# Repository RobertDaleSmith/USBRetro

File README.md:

# Joypad OS

<p align="center">
  <picture>
    <source media="(prefers-color-scheme: dark)" srcset="docs/images/logo_solid.svg">
    <source media="(prefers-color-scheme: light)" srcset="docs/images/logo_solid_black.svg">
    
  </picture>
</p>

**Universal controller firmware foundation for adapters, controllers, and input systems.**

Joypad OS is a modular, high-performance firmware platform for building controller adapters, custom controllers, and input/output bridges across USB, Bluetooth, and native game console protocols.

Formerly known as **USBRetro**, this project now serves as the foundational firmware layer of the **Joypad** ecosystem — a universal platform for extending how controllers work, connect, and evolve.

Joypad OS focuses on real-time controller I/O, protocol translation, and flexible routing, making it easy to build everything from classic console adapters to next-generation, assistive, and AI-augmented input devices.

---

## What Joypad OS Enables

- **Universal input/output translation** — Convert USB HID devices into native console protocols and vice versa.
- **Modular firmware apps** — Build specific bridges like `usb2usb`, `usb2gc`, `snes2usb`, passthrough adapters, merged inputs, and hybrid devices — all on a shared core.
- **Flexible routing & passthrough** — Support multi-output controllers, input merging, chaining devices, and advanced mods.
- **Hardware-agnostic foundation** — Designed to run across RP2040 today, with future portability to ESP32 and nRF platforms.
- **Foundation for accessibility & assistive play** — Enables custom controllers and input extensions for gamers with diverse needs.

Joypad OS is the real-time nervous system of the Joypad platform.

---

## Supported Outputs

| Output | Features | Documentation |
|--------|----------|---------------|
| **USB Device** | HID Gamepad, XInput, Xbox OG, Xbox One, PS3, PS4, PS Classic, Switch | [Docs](docs/BUILD.md) |
| **PCEngine / TurboGrafx-16** | Multitap (5 players), Mouse, 2/3/6-button | [Docs](docs/consoles/PCENGINE.md) |
| **GameCube / Wii** | Profiles, Rumble, Keyboard mode | [Docs](docs/consoles/GAMECUBE.md) |
| **Nuon DVD Players** | Controller, Spinner (Tempest 3000), IGR | [Docs](docs/consoles/NUON.md) |
| **3DO Interactive Multiplayer** | 8 players, Mouse, Extension passthrough | [Docs](docs/consoles/3DO.md) |
| **Casio Loopy** | 4 players (experimental) | [Docs](docs/consoles/LOOPY.md) |

---

## Products

Pre-built adapters available at **[controlleradapter.com](https://controlleradapter.com)**:

- **[USB-2-PCE](https://controlleradapter.com/products/usb-2-pce)** - PCEngine/TurboGrafx-16 adapter
- **[GC USB](https://controlleradapter.com/products/gc-usb)** - GameCube/Wii adapter with profiles
- **[NUON USB](https://controlleradapter.com/products/nuon-usb)** - Nuon DVD player adapter

---

## Supported USB Devices

**Controllers:**
- Xbox (OG/360/One/Series X|S)
- PlayStation (Classic/DS3/DS4/DualSense)
- Nintendo Switch (Pro/Joy-Cons)
- 8BitDo (PCE 2.4g, M30, Adapters)
- Generic HID gamepads

**Peripherals:**
- USB Keyboards (full HID support)
- USB Mice (PCEngine mouse, Nuon spinner, 3DO mouse)
- USB Hubs (up to 8 devices for 3DO)

**[Complete hardware compatibility list](docs/HARDWARE.md)**

---

## For Users: Updating Firmware

### Quick Flash

1. **Download** latest `.uf2` from [Releases](https://github.com/joypad-ai/joypad-os/releases)
2. **Enter bootloader**:
   - **USB-2-PCE / NUON / 3DO**: Hold BOOT + connect USB-C
   - **GC USB**: Just connect USB-C (no button)
3. **Drag** `.uf2` file to `RPI-RP2` drive
4. **Done!** Drive auto-ejects when complete

**[Full installation guide](docs/INSTALLATION.md)**

---

## For Developers: Building Firmware

### Quick Start

```bash
# Install ARM toolchain (macOS)
brew install --cask gcc-arm-embedded cmake git

# Clone and initialize
git clone https://github.com/joypad-ai/joypad-os.git
cd joypad-os && make init

# Build specific product
make usb2gc         # GameCube adapter
make usb2pce        # PCEngine adapter
make usb2nuon       # Nuon adapter
make usb23do        # 3DO adapter
```

### Build Commands

```bash
make init          # Initialize submodules (one-time setup)
make all           # Build all products
make clean         # Clean build artifacts

# Build specific products
make usb2pce       # USB2PCE (KB2040 + PCEngine)
make usb2gc        # USB2GC (KB2040 + GameCube)
make usb2nuon      # USB2Nuon (KB2040 + Nuon)
make usb23do       # USB23DO (KB2040 + 3DO)
make usb2loopy     # USB2Loopy (KB2040 + Casio Loopy)
make snes23do      # SNES23DO (SNES→3DO bridge)
```

Output firmware files appear in `releases/` directory.

**[Complete build guide](docs/BUILD.md)**

---

## Documentation

- **[Installation Guide](docs/INSTALLATION.md)** - Flashing firmware, troubleshooting
- **[Hardware Compatibility](docs/HARDWARE.md)** - Supported controllers, boards, DIY builds
- **[Build Guide](docs/BUILD.md)** - Developer setup, architecture

### Console-Specific Guides

- **[GameCube/Wii](docs/consoles/GAMECUBE.md)** - Profiles, keyboard mode, rumble
- **[PCEngine/TurboGrafx-16](docs/consoles/PCENGINE.md)** - Multitap, mouse, button modes
- **[Nuon](docs/consoles/NUON.md)** - Controller, Tempest 3000 spinner, IGR
- **[3DO](docs/consoles/3DO.md)** - 8-player support, mouse, profiles
- **[Casio Loopy](docs/consoles/LOOPY.md)** - Experimental support

---

## Architecture

Joypad OS uses a modular architecture:

- **RP2040** - Dual-core ARM Cortex-M0+ microcontroller
- **TinyUSB** - USB host stack for polling USB devices
- **PIO** - Programmable I/O for timing-critical console protocols
- **Dual-Core**: Core 0 handles USB input, Core 1 runs console output
- **Router** - Flexible input→output routing (SIMPLE/MERGE/BROADCAST)
- **Apps** - Per-product configuration (router, profiles, features)

**See [CLAUDE.md](CLAUDE.md) for detailed architecture**

---

## Community & Support

- **Discord**: [community.joypad.ai](http://community.joypad.ai/) - Community chat
- **Issues**: [GitHub Issues](https://github.com/joypad-ai/joypad-os/issues) - Bug reports
- **Email**: support@controlleradapter.com - Product support

---

## Acknowledgements

- [Ha Thach](https://github.com/hathach/) - [TinyUSB](https://github.com/hathach/tinyusb)
- [David Shadoff](https://github.com/dshadoff) - [PCEMouse](https://github.com/dshadoff/PC_Engine_RP2040_Projects/tree/main/PCEMouse) foundation
- [FCare](https://github.com/FCare) - [USBTo3DO](https://github.com/FCare/USBTo3DO) 3DO protocol implementation
- [Ryzee119](https://github.com/Ryzee119) - [tusb_xinput](https://github.com/Ryzee119/tusb_xinput/)
- [SelvinPL](https://github.com/SelvinPL/) - [lufa-hid-parser](https://gist.github.com/SelvinPL/99fd9af4566e759b6553e912b6a163f9)
- [JonnyHaystack](https://github.com/JonnyHaystack/) - [joybus-pio](https://github.com/JonnyHaystack/joybus-pio)

---

## License

Joypad OS is licensed under the **Apache-2.0 License**.

The **Joypad** name and branding are trademarks of Joypad Inc.

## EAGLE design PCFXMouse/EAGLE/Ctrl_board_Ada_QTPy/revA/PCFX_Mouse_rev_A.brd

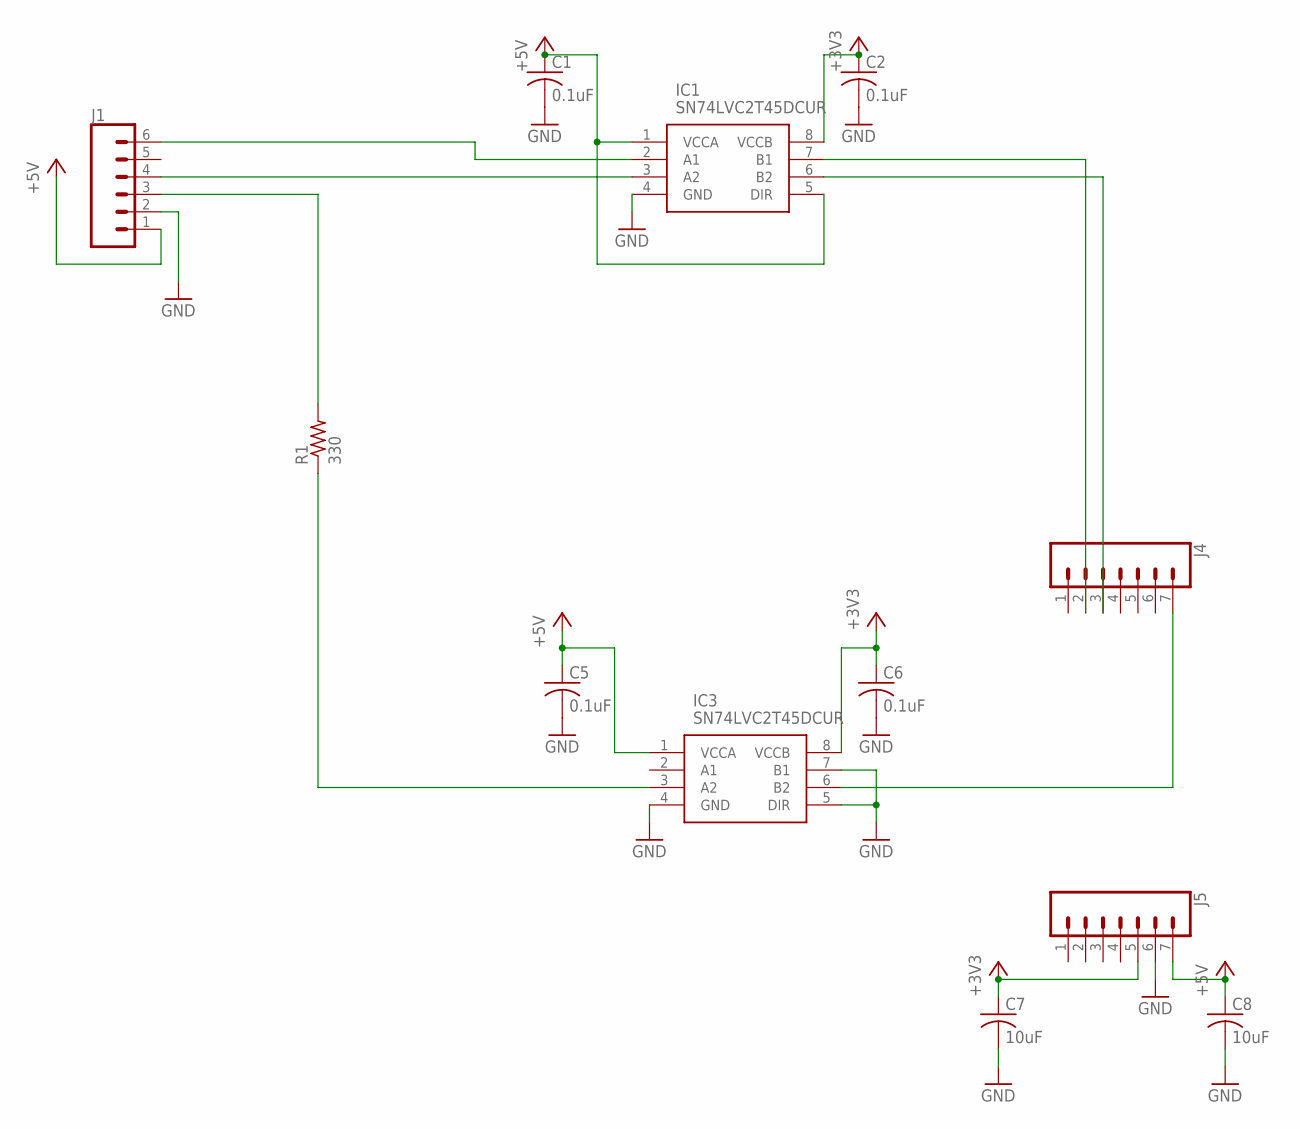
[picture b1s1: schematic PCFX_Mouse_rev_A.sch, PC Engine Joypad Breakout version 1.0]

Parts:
C1, C2, C5, C6: 0.1uF; C0402
C7, C8: 10uF; C0805
IC1, IC3: SN74LVC2T45DCUR; SOP50P310X90-8N
J1: CONN_06NO_SILK_FEMALE_PTH; 1X06_NO_SILK
J4, J5: CONN_07LONGPADS; 1X07_LONGPADS
R1: 330; R0402

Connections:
+3V3: C2.1, C6.1, C7.1, IC1.8 (VCCB), IC3.8 (VCCB), J5.5
+5V: C1.1, C5.1, C8.1, IC1.1 (VCCA), IC1.5 (DIR), IC3.1 (VCCA), J1.1, J5.7
CLK: IC1.3 (A2), J1.4
DATA: J1.3, R1.2
GND: C1.2, C2.2, C5.2, C6.2, C7.2, C8.2, IC1.4 (GND), IC3.4 (GND), IC3.5 (DIR), IC3.7 (B1), J1.2, J5.6
LATCH: IC1.2 (A1), J1.6
unnamed: IC1.7 (B1), J4.2
unnamed: IC3.6 (B2), J4.7
unnamed: IC1.6 (B2), J4.3
unnamed: IC3.3 (A2), R1.1

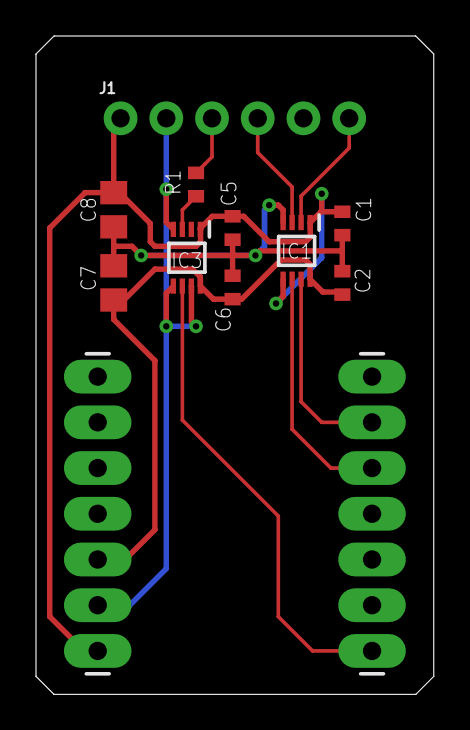
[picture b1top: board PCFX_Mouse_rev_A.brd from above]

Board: 2 copper layers, 22.1 x 36.6 mm, 12 parts (0 on the bottom side), 10 nets.

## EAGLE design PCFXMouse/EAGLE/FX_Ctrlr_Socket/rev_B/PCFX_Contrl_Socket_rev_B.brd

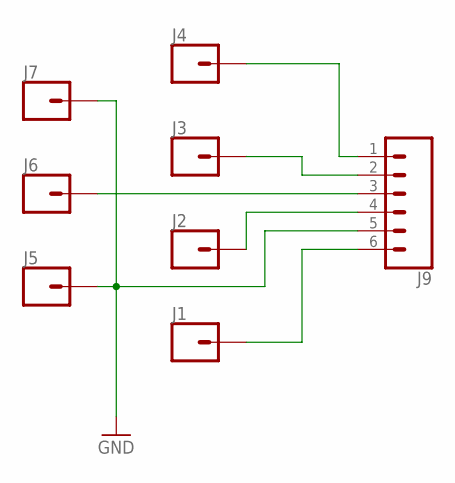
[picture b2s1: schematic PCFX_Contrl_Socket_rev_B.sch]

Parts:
J1, J2, J3, J4, J5, J6, J7: CONN_01PTH_NO_SILK_YES_STOP; 1X01_NO_SILK
J9: CONN_06NO_SILK_FEMALE_PTH; 1X06_NO_SILK

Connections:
GND: J5.1, J7.1, J9.5
unnamed: J4.1, J9.1
unnamed: J3.1, J9.2
unnamed: J6.1, J9.3
unnamed: J2.1, J9.4
unnamed: J1.1, J9.6

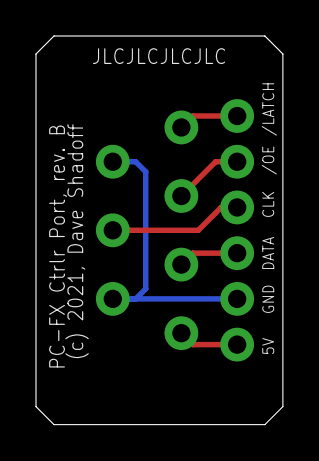
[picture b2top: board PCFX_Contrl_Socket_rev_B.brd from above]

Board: 2 copper layers, 13.7 x 21.6 mm, 8 parts (0 on the bottom side), 6 nets.

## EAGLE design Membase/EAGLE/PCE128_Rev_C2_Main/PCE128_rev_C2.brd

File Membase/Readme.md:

# PC_Engine_RP2040_Projects - Memory Base 128 reimplementation

## Overview

This is the third implementation of the Memory Base 128 I have written for modern hardware, and the easiest code to read/follow.
The PIOs on the Raspberry Pi Pico microcontroller are used for edge-sensing of the data input, and the ARM core is used for processing.

The data is loaded into SRAM at startup, and saved into Flash after transactions take place.  This may not be ideal, as the
device is not capable of processing additional commands while the Flash flush is in progress (it takes place 0.75 seconds
after the last read/write of a group of read or write transactions).  While this flush is taking place, the PIO state machine
is shut down, so there won't be a backlog of bits causing confusion; however, if any transactions take place during the period of
flash write, they won't be recognized, and the PC Engine game may identify an error.

Status is displayed by LEDs on the main board, recessed into the device, adjacent to the joypad connector:

Yellow (Left) = Device active  
Green (Right) = Read  
Red (Right) = Write  
Blue (Left) = Delayed commit to Flash memory  

## Source Code

This was built using Pico-SDK version 1.2.0
pico_sdk_import.cmake is from the SDK, but is required by CMake (and thus replicated here)

To build the source, first ensure that you have the right version of the RaspberryPi/piso-sdk installed.
As this board targets the Adafruit QtPy2040 board, you should run the make_ada.sh script (under UNIX), or from
the command-line:  
"cmake -DPICO_BOARD=adafruit_qtpy_rp2040 -B build"  
Then, "cd build" and "make".

I have also included a release version of the program as a uf2 file in the releases/ folder; just drag and drop it
onto the virtual drive presented when putting the board into BOOTSEL mode (holding the 'boot' button, connect the
board by USB to a host computer, and release the button; a new drive should appear on the computer).

## PC Board & Assembly

I designed all boards using the free version of EAGLE (2-layer, less than 100mm on both X- and Y- axes).
The gerbers are included in this repository, in case you want to get your own set made.

I have included the gerbers and relevant bom.csv and assembly.csv files to get these boards
assembled by JLCPCB, but you will still need the following parts:
- (2) 8-pin Mini-DIN connectors
- (1) Adafruit QtPy RP2040 microcontroller board
- (2) 7-pin headers.  You may also want to use female pin header sockets in case you need to remove the microcontroller board.
I recommend using short/low-profile header sockets in this case.

You will also need some mounting hardware for the board stack-up:
- (4) M3 x 13mm female-female standoffs; flat side-to-flat side should be no larger tha 5.0mm, as the mounting holes are made for this size.  (4.5mm are fine too)
- (8) M3 screws, 6mm in length (*) - these may need to be longer if you don't trim the through-hole leads flush to the board.
- optional rubber/silicone feet

And for use, you will also need a short 8-pin mini-DIN male-male cable (various lengths can be found on ebay).

### Assembly

The "case" is made up of stacked PC boards, with PC boards on the top and bottom; There are 5 different boards in all, but 13 layers as follows:
1. Top = 1 layer, 1.6mm thick, ENIG board, in "PCE128_Rev_C_Face"  
2. MidTop = 6 layers, 1.6mm thick, HASL board in "PCE128_Rev_C_MidTop"  
3. MidLow = 3 layers, 1.2mm thick, HASL board in "PCE128_Rev_C_MidLow" (looks similar to MidTop, but has cutouts for the LEDs)  
4. Main Board = 1 layer, 1.6mm thick, HASL, SMD assembly board in "PCE128_Rev_C2_Main" (Note: some parts have been shifted from the previous "B" version; they are not interchangeable)  
5. Sub = 1 layer, 0.8mm thick (*), HASL board in "PCE128_Rev_C_Sub"  
6. Bottom = 1 layer, 1.6mm thick, ENIG board in "PCE128_Rev_C_Face" (reverse side faces out)  

(*) Note that I trim the through-hole leads flush to the board, which enables a thin "Sub" layer, which exists only to make space for the through-hole portions; if you do not trim these flush, you may need a much thicker Sub layer, and longer M3 screws.

Steps to assembly:
1. Trim the leads of the through-hole parts carefully, to minimize the solder "bump" on the underside of the board when mounted.  The through-hole parts to be mounted include the 8-pin mini-DIN sockets, and the headers (or sockets) for the RP2040 board.  **Make sure that the mini-DIN connectors are mounted straight, or the upper-layer boards may have trouble being placed.**
2. Solder carefully, miniizing the amount of "bump" below the board
3. With the LEDs closest to you, mount the RP2040 board with the USB connector on the right side
4. Connect it to a host computer while holding the "Boot" button down.  This will put it in DFU mode and create a virtual drive on the host computer.  Drag and drop the *.uf2 firmware file into that folder.  A moment later, the virtual drive should disappear and after about 1 second, all four LEDs should light up briefly as part of the boot sequence of the memory device.  Disconnect it from USB.

For the board stack-up, it is best to connect the lower boards first, with the screws going through the bottom layers of board, into one side of the female-female standoffs.  Then, the upper layer boards can simply be stacked, and the top screws tightened easily.

And one final touch: the edges of the PC boards are a different shade than the front/back surfaces, creating a two-tone effect which you may or may not like.  In order to make the case look more like a uniform "black box", I have used a Sharpie marker along the edge of the PC Boards to darken them.  The shade is similar to JLCPCB's matte black solder mask, so it should be a good match in areas with standard lighting.  The Sharpie ink, being permanent, won't run when it gets wet, but be careful near any alcohol-based solvents; the ink may run/stain in such situations.

Here is a visual view:

## Notes
I have tried to use the Adafruit QtPy RP2040 as much as possible, as it is a compact form factor which is easy to design around.

Unfortunately, the Adafruit site tries to direct all users toward CircuitPython rather than the Pi SDK, and
as a result, Pinout pages of the "Pinout" page for their RP2040 devices don't include references to the GPIO numbers.

Therefore, I am including a graphic here:

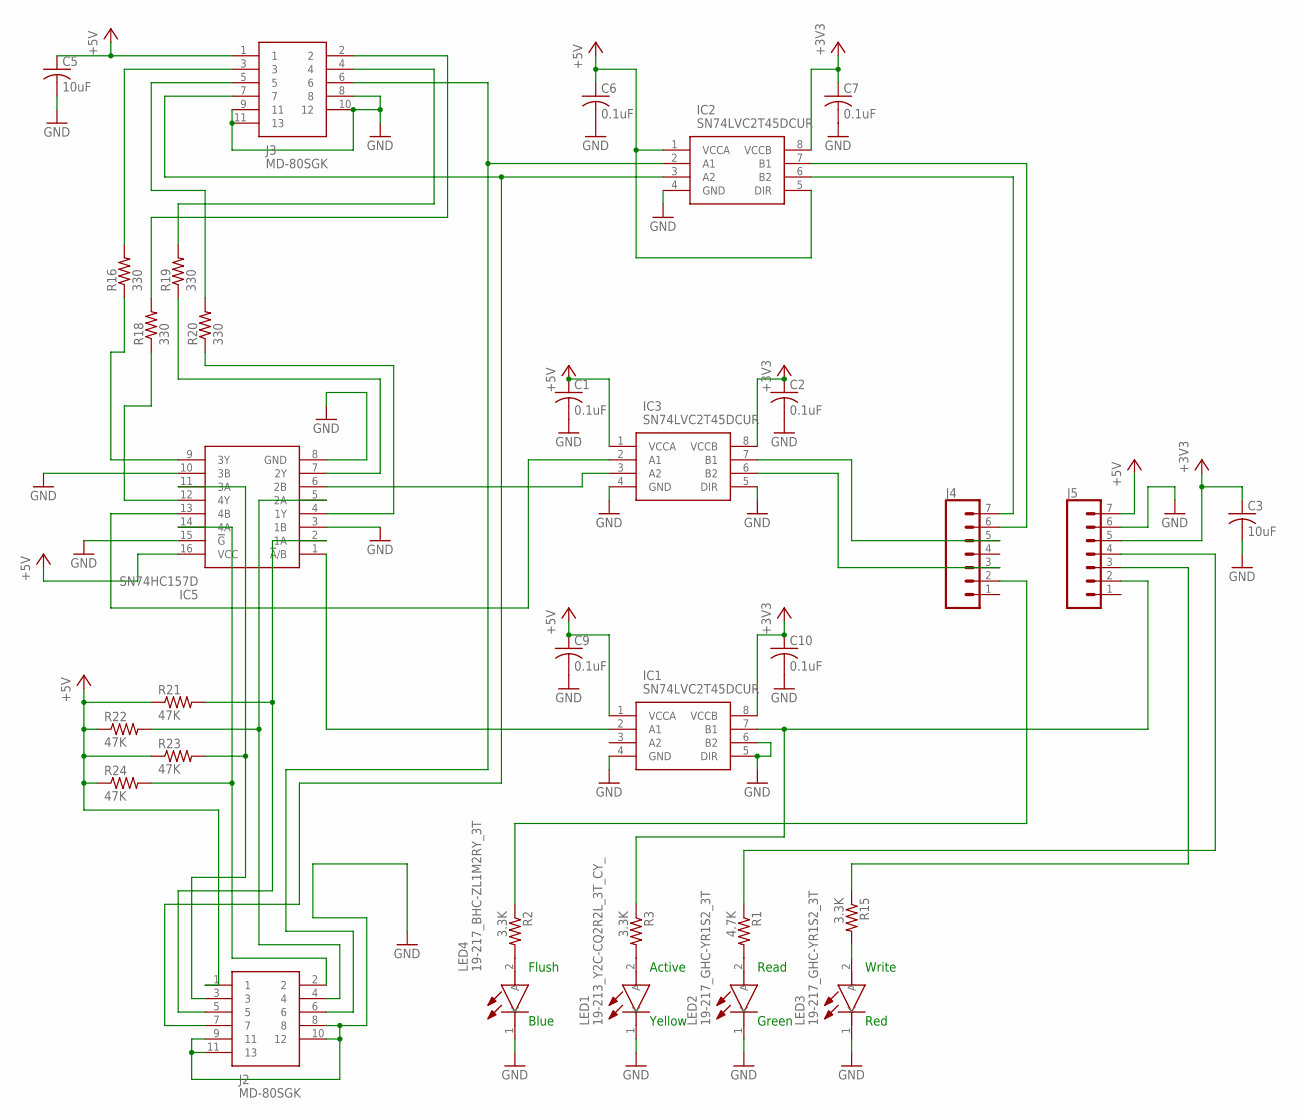
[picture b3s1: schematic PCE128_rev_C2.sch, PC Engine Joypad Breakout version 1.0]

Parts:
C1, C2, C6, C7, C9, C10: 0.1uF; C0402
C3, C5: 10uF; C0805
IC1, IC2, IC3: SN74LVC2T45DCUR; SOP50P310X90-8N
IC5: SN74HC157D; SOIC127P600X175-16N
J2, J3: MD-80SGK; MD80SGK
J4, J5: CONN_07NO_SILK; 1X07_NO_SILK
LED1: 19-213_Y2C-CQ2R2L_3T_CY_; LEDC1608X50N
LED2: 19-217_GHC-YR1S2_3T; LEDC1608X50N
LED3: 19-217_GHC-YR1S2_3T; LEDC1608X50N; MANUFACTURER_PART_NUMBER KT-0603R
LED4: 19-217_BHC-ZL1M2RY_3T; LEDC1608X50N
R1: 4.7K; R0402
R2, R3, R15: 3.3K; R0402
R16, R18, R19, R20: 330; R0402
R21, R22, R23, R24: 47K; R0402

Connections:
+3V3: C2.1, C3.1, C7.1, C10.1, IC1.8 (VCCB), IC2.8 (VCCB), IC3.8 (VCCB), J5.5
+5V: C1.1, C5.1, C6.1, C9.1, IC1.1 (VCCA), IC2.1 (VCCA), IC2.5 (DIR), IC3.1 (VCCA), IC5.16 (VCC), J2.1, J3.1, J5.7, R21.1, R22.1, R23.1, R24.1
CLR: IC2.3 (A2), J2.7, J3.7
D0_IN: IC5.14 (4A), J2.2, R24.2
D0_OUT: J3.2, R18.2
D1_IN: IC5.11 (3A), J2.3, R23.2
D1_OUT: J3.3, R16.2
D2_IN: IC5.5 (2A), J2.4, R22.2
D2_OUT: J3.4, R19.2
D3_IN: IC5.2 (1A), J2.5, R21.2
D3_OUT: J3.5, R20.2
D6: J5.3, R15.1
D10: J5.4, R1.1
D11: IC1.7 (B1), J5.2, R3.1
GND: C1.2, C2.2, C3.2, C5.2, C6.2, C7.2, C9.2, C10.2, IC1.4 (GND), IC1.5 (DIR), IC1.6 (B2), IC2.4 (GND), IC3.4 (GND), IC3.5 (DIR), IC5.3 (1B), IC5.8 (GND), IC5.10 (3B), IC5.15 (!G), J2.8, J2.9 (11), J2.10 (12), J2.11 (13), J3.8, J3.9 (11), J3.10 (12), J3.11 (13), J5.6, LED1.1 (K), LED2.1 (K), LED3.1 (K), LED4.1 (K)
unnamed: LED2.2 (A), R1.2
unnamed: J4.2, R2.1
unnamed: IC3.7 (B1), J4.5
unnamed: LED4.2 (A), R2.2
unnamed: LED1.2 (A), R3.2
unnamed: IC3.6 (B2), J4.3
unnamed: IC3.3 (A2), IC5.6 (2B)
unnamed: IC2.7 (B1), J4.6
unnamed: IC1.2 (A1), IC5.1 (!A!/B)
unnamed: IC5.9 (3Y), R16.1
unnamed: IC5.12 (4Y), R18.1
unnamed: IC5.4 (1Y), R20.1
unnamed: IC5.7 (2Y), R19.1
unnamed: IC3.2 (A1), IC5.13 (4B)
unnamed: IC2.6 (B2), J4.7
unnamed: LED3.2 (A), R15.2
SEL: IC2.2 (A1), J2.6, J3.6

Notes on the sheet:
Active
Read
Write
Yellow
Green
Red
Blue
Flush

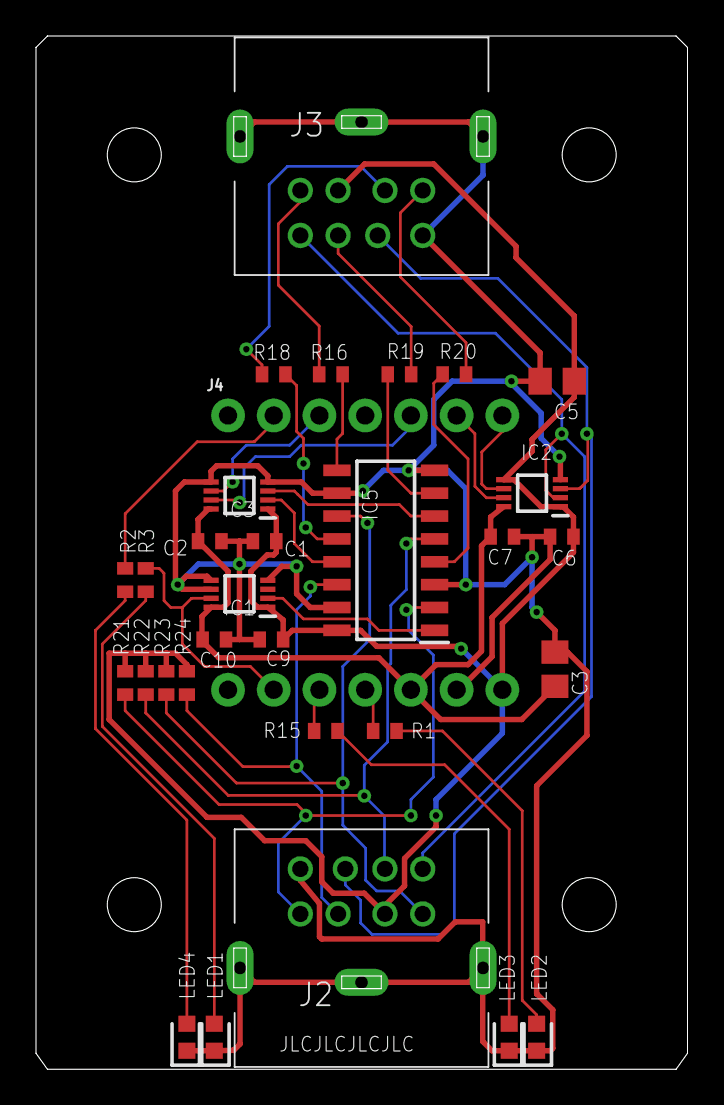
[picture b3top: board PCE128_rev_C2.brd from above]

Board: 2 copper layers, 36.2 x 57.4 mm, 32 parts (0 on the bottom side), 32 nets.

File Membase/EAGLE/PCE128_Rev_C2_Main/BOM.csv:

Qty,Designator,Footprint,Comment,LCSC Part # (optional),Description (optional)
2,"J2, J3",MD80SGK,Do not mount,Do not mount,"Circular DIN Connectors mini-DIN, 8P jack, rt, through hole, full shield"
2,"J4, J5",1X07_NO_SILK,Do not mount,Do not mount,Multi connection point. Often used as Generic Header-pin footprint for 0.1 inch spaced/style header connections
6,"C1, C2, C6, C7, C9, C10",C0402,100nF 16V,C1525,Samsung CL05B104KO5NNNC 100nF 16V 0402
2,"C3, C5",C0805,10uF 25V,C15850,Samsung CL21A106KAYNNNE  10uF 25V 0805
1,LED1,LEDC1608X50N,Yellow,C72038,Everlight Elec 19-213/Y2C-CQ2R2L/3T(CY)  0603
1,LED2,LEDC1608X50N,Green,C72043,Everlight Elec 19-217/GHC-YR1S2/3T  0603
1,LED3,LEDC1608X50N,Red,C2286,Hubei KENTO Elec  KT-0603R  0603
1,LED4,LEDC1608X50N,Blue,C72041,Everlight 19-217/BHC-ZL1M2RY/3T  0603
1,R1,R0402,4.7K,C25900,Uniroyal Elec  0402WGF4701TCE  0402
3,"R2, R3, R15",R0402,3.3K,C25890,Uniroyal Elec  0402WGF3301TCE  0402
4,"R16, R18, R19, R20",R0402,330R,C25104,Uniroyal Elec  0402WGF3300TCE  0402
4,"R21, R22, R23, R24",R0402,47K,C25792,Uniroyal Elec  0402WGF4702TCE  0402
3,"IC1, IC2, IC3",VSSOP-8_2.0x2.3x0.5P,SN74LVC2T45DCUR,C15741,"Texas Instruments SN74LVC2T45DCUR, Voltage Level Translator, Bus Transceiver, 3-State, 1.65  5.5 V, 8-Pin UM"
1,IC5,SOIC-16_3.9x9.9x1.27P,SN74HC157D,C6823,Quadruple 2-Line To 1-Line Data Selectors/Multiplexers

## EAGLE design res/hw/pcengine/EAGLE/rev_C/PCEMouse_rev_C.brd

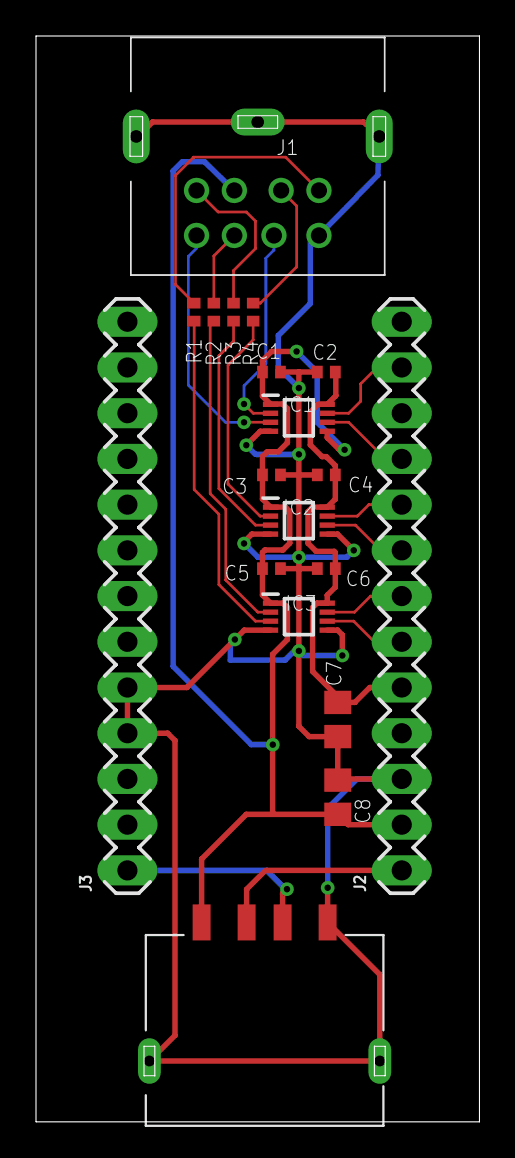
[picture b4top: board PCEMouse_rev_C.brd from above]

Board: 2 copper layers, 24.6 x 60.3 mm, 19 parts (0 on the bottom side), 21 nets.

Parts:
C1, C2, C3, C4, C5, C6: 0.1uF; C0402
C7, C8: 10uF; C0805
IC1, IC2, IC3: SN74LVC2T45DCUR; SOP50P310X90-8N
J1: MD-80SGK; MD80SGK
J2, J3: 1X13-LONGPADS
R1, R2, R3, R4: 330; R0402
U$1: 912-121A2026S10100

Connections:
+3V3: C2.1, C4.1, C6.1, C7.1, IC1.8, IC2.8, IC3.8, J2.5
+5V: C1.1, C3.1, C5.1, C8.1, IC1.1, IC1.5, IC2.1, IC3.1, J1.1, J2.2, U$1.VCC
CLR: IC1.2, J1.7
D0_OUT: J1.2, R4.2
D1_OUT: J1.3, R3.2
D2_OUT: J1.4, R2.2
D3_OUT: J1.5, R1.2
GND: C1.2, C2.2, C3.2, C4.2, C5.2, C6.2, C7.2, C8.2, IC1.4, IC2.4, IC2.5, IC3.4, IC3.5, J1.8, J1.9, J1.10, J1.11, J2.3, J3.4, J3.5, U$1.GND, U$1.P$5, U$1.P$6
GPIO18: IC1.6, J2.10
GPIO19: IC1.7, J2.12
GPIO26: IC2.7, J2.9
GPIO27: IC2.6, J2.8
GPIO28: IC3.7, J2.7
GPIO29: IC3.6, J2.6
unnamed: J3.1, U$1.D+
unnamed: IC3.3, R1.1
unnamed: IC3.2, R2.1
unnamed: IC2.3, R3.1
unnamed: IC2.2, R4.1
unnamed: J2.1, U$1.D-
SEL: IC1.3, J1.6

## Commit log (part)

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2025-12-05 Add missing app_task to snes23do
2025-12-05 Add usb2usb_rp2040zero target for RP2040-Zero boards
    Adds support for USB host on RP2040-Zero with PIO USB pins:
    - D+ on GPIO 10, D- on GPIO 11 (compatible with ogx-mini hardware)
    - NeoPixel on GPIO 16
    PIO USB pin configuration is now defined at the board/target level
    via CONFIG_PIO_USB_DP_PIN, making it easy to add other board variants.
    Build with: make usb2usb_rp2040zero
2025-12-05 Add button GPIO definition for usb2usb_rp2040zero (GPIO 14)
2025-12-05 Refactor CMakeLists.txt to reduce duplication
    - Add source lists (CORE_SOURCES, USB_HOST_SOURCES, USB_DEVICE_SOURCES, etc.)
    - Add library lists (COMMON_LIBRARIES, CONTROLLER_LIBRARIES)
    - Add helper function usbretro_target_common() for common target setup
    - Organize targets into sections by app type
    - Reduce file from ~675 lines to ~432 lines
2025-12-10 Fix L1/R1/L2/R2 button mapping in PSC output interface
2025-12-11 Add DS3 Bluetooth support
    - DS3 BT driver with enable_sixaxis activation and input parsing
    - Skip authentication for DS3 (uses COD-based detection)
    - ACL deferred send pattern for USB endpoint busy handling
    - USB DS3 programming flow: wait for button press, program dongle address
    - Cache local BD_ADDR to flash for DS3 programming when dongle unplugged
    - Add bt_task() call to main loop for BT HID driver tasks
2025-12-11 Add rumble support for DS3 Bluetooth
2025-12-12 Add separate left/right rumble and LED feedback to output interface
2025-12-12 Add motion data passthrough for DS3/DS4/DS5 controllers
    - Add accel[3], gyro[3], has_motion fields to input_event_t and profile_output_t
    - Parse motion data in DS3 USB/BT drivers (bytes 40-47, big-endian 16-bit)
    - Parse motion data in DS4/DS5 USB/BT drivers from existing struct fields
    - Output motion in PS3 output interface with big-endian byte order
    - Fix router MERGE_BLEND mode to copy motion from first device with motion data
    - Adjust PS3 input report to 50 bytes for correct motion byte alignment
2025-12-12 Add DS3 pressure-sensitive button passthrough
    Parse all 12 pressure values from DS3 USB and BT input reports:
    - D-pad: up, right, down, left
    - Triggers/bumpers: L2, R2, L1, R1
    - Face buttons: triangle, circle, cross, square
    Added pressure[12] and has_pressure to input_event_t and
    profile_output_t. PS3 output mode now uses actual pressure
2025-12-12 Add stick modifier system for button-triggered sensitivity changes
    - Add stick_modifier_t struct for button-triggered sensitivity modifiers
    - Add left/right_stick_modifiers arrays to profile_t
    - Update profile_apply() to check modifiers before applying sensitivity
    - First matching modifier wins, can optionally consume trigger button
    - Add STICK_MODIFIER() and STICK_MODIFIER_KEEP() helper macros
    - SSBM profile: L3 reduces left stick to 50% for walk mode
2025-12-12 Rename USBRetro to Joypad
    - USBR_BUTTON_* → JP_BUTTON_* across all files
    - USBRetro references → Joypad in comments/strings
    - Completes rebranding to match new project name
2025-12-12 Add ASCII controller diagram to buttons.h
    Shows button positions with W3C index numbers for quick reference.
2025-12-12 Add A4 placeholder button
2025-12-12 Update README for Joypad Core rebrand
2025-12-12 Update repo URLs to joypad-ai/joypad-core
2025-12-12 Remove Xbox One S from supported consoles
2025-12-12 Remove DragonRise from supported devices
2025-12-12 Update CLAUDE.md: add flash commands, profile system, USBRetro context; remove USB-2-3DO product
2025-12-12 Rename Supported Consoles to Supported Outputs, add USB HID
2025-12-12 Add Xbox One to USB outputs
2025-12-12 DS4 BT: add rumble, motion, LED support; rename USBR to Joypad
    - Add feedback system integration for rumble passthrough
    - Add motion data passthrough (gyro/accel) when sixaxis enabled
    - Add player LED colors: P1=blue, P2=red, P3=green, P4=pink
    - Support both RGB LED and player LED pattern from host
    - Activation state machine with proper delays
    - Rename USB device strings: USBR → Joypad (DInput, XAC, Data, Debug)
2025-12-12 BLE: Add extended scanning and connection for Xbox Series controllers
    - Add BLE extended scanning (HCI 0x2041/0x2042) for BT 5.0+ dongles
    - Add LE Extended Create Connection (0x2043) command
    - Fix HCI event mask to include LE Meta Event (bit 61)
    - Parse BLE advertising data to extract device names
    - Auto-detect and connect to Xbox Wireless Controller
    - Proper sequencing: cancel inquiry -> stop scan -> connect
2025-12-13 BLE: Add SMP pairing for encrypted HID access
    Xbox BLE controllers require encryption before allowing HID access.
    When ATT receives error 0x0F (Insufficient Encryption), SMP pairing
    is automatically initiated.
    SMP Implementation:
    - "Just Works" pairing (no user interaction required)
    - AES-128 encryption for c1 confirm and s1 STK generation
2025-12-15 BTstack: Use standard listener API, remove gatt_client.c hook
    Switch from custom gatt_client.c hook to standard BTstack API:
    - gatt_client_listen_for_characteristic_value_updates() works correctly
    - Register listener after SM_EVENT_PAIRING_COMPLETE and REENCRYPTION_COMPLETE
    - Deferred processing pattern preserved (copy to buffer, process in main loop)
    Root cause of previous freeze was printf inside __not_in_flash_func,
    not the BTstack listener API itself.
2025-12-15 BTstack: Add Classic BT HID Host support
    Wire BTstack's hid_host.c to existing bthid driver layer:
    - Initialize hid_host_init() with HID descriptor storage
    - Add classic inquiry scanning alongside BLE scanning
    - Handle GAP_EVENT_INQUIRY_RESULT to detect gamepads (COD 0x05xx)
    - Auto-connect to gamepads/joysticks with hid_host_connect()
    - Handle HID_SUBEVENT_* events for connection lifecycle:
2025-12-15 Implement user button hold to clear all BT bonds
    - Add btstack_host_delete_all_bonds() to clear Classic and BLE bonds
    - Hold user button (1.5s) triggers bond clearing
    - Clears Classic BT link keys via gap_delete_all_link_keys()
    - Clears BLE bonds via le_device_db_init()
2025-12-15 Fix DS4/DS5 Bluetooth reconnection
    - Add SDP server with Device ID record (required for Sony reconnect)
    - Handle link key storage and reply manually for incoming connections
    - Request remote name on incoming for proper driver matching
    - Let device initiate HID channels on reconnect (not host)
2025-12-16 Query SDP VID/PID for outgoing Classic BT connections
    Previously SDP Device ID query was only triggered for incoming
    connections. Now also query VID/PID when HID connection opens
    for outgoing (inquiry-based) connections.
    - Start SDP query at HID_SUBEVENT_CONNECTION_OPENED if VID/PID unknown
    - Request remote name if not available from inquiry EIR data
    - Update connection struct when SDP query and name request complete
2025-12-16 feat: BTstack modularization, PCEngine fixes, wired chatpad support
    BTstack improvements:
    - Refactor BTstack to modular usbretro_add_btstack() CMake function
    - Move BT initialization from app to usbh layer for consistency
    - Make CFG_TUH_BTD conditional on ENABLE_BTSTACK define
    - Fix hal_cpu_enable_irqs_and_sleep() blocking on console targets
    - Enable BTstack on PCE and NGC targets for investigation
2025-12-17 PCE: Add left analog stick to d-pad mapping
2025-12-17 BTstack: Enable on all targets, add Broadcom support, document dongle compatibility
    - Enable BTstack on all USB host console targets (nuon, loopy, 3do, uart, usb_rp2040zero)
    - Add Broadcom dongle support (vendor-specific class 0xFF with VID 0x0A5C)
    - Add comprehensive dongle compatibility guide in hci_transport_h2_tinyusb.h
    - Documents chipset compatibility (Broadcom/CSR work, Realtek needs firmware)
    - Lists tested dongles with VID/PID and chip info
    - Buying recommendations for embedded use
2025-12-18 Rename build targets to joypad, add board to app names
    - Rename cmake targets from usbretro_* to joypad_*
    - Rename output files from usbr_* to joypad_*
    - Add board name to all app targets (e.g., usb2gc_kb2040)
    - Add usb2gc_rp2040zero target for GameCube on RP2040-Zero
    - Add persistent flash-based link key storage for BTstack USB dongle
    - Expand RELEASE_APPS to include all stable apps
2025-12-18 Fix profile switching feedback and hotkey detection
    Feedback system:
    - Add feedback_init() to player manager initialization
    - Add internal setters (feedback_set_rumble_internal, etc.) that bypass
    profile indicator check, used by profile_indicator.c
    - Public setters now block external updates during profile indication,
    preventing apps from overwriting rumble/LED pulses
2025-12-18 Add Google Stadia controller support
    - New USB HID driver for Stadia controller (VID 0x18D1, PID 0x9400)
    - Input: D-pad, face buttons, shoulders, analog triggers, sticks, system buttons
    - Output: 16-bit rumble motors via report ID 0x05
    - Same report format works for both USB and Bluetooth modes
2025-12-18 Fix bt2usb: Use bt_init() and bt_task() for proper driver registration
    bt2usb was directly calling bt_transport_cyw43.init() and .task(),
    which bypassed the bt_init() function that:
    - Sets global bt_transport pointer (needed for bt_get_connection())
    - Calls bthid_registry_init() to register all BT HID drivers
    Without this, bt_get_connection() returned NULL and no drivers
    (DS5, DS4, etc.) were registered, causing input to not be processed.
2025-12-19 Fix BT disconnect: clear held buttons and free player slots
    - Add router_device_disconnected() to send zeroed input on disconnect
    - Fix BLE disconnect handler to call bt_on_disconnect() with correct conn_index
    - Add missing remove_players_by_address() calls to Switch/Xbox BT drivers
    - Add Pico 2 W support for bt2usb
2025-12-20 Fix rp2040zero GameCube build: remove PIO USB and override I2C pins
    - Remove PIO USB to avoid PIO0 conflict with joybus protocol
    - Override default I2C pins (6/7 -> 14/15) to avoid conflict with
    GameCube pins (GC_DATA=7, GC_3V3=6)
2025-12-22 Add rumble and player LED passthrough for Switch Pro controllers
    Switch 2 Pro:
    - Add haptic output via HID Report ID 0x02
    - Send haptic updates continuously (50ms interval) while rumble active
    - Add player LED output via bulk endpoint
    - Pass through rumble intensity with minimum threshold boost
    Switch Pro:
2025-12-22 Fix player LED passthrough for Switch Pro from USB output interface
    - Derive player_index from feedback LED pattern instead of profile indicator
    - Add rumble encoding to LED command (CMD_AND_RUMBLE needs rumble bytes)
    - Initialize rumble/player_led to 0xFF in init to trigger first update
    - Use config->player_index from output interface instead of find_player_index()
2025-12-22 Fix PS3 SIXAXIS neutral value to 512 for zero pitch/roll
    Changed IMU neutral from 511 (0x01FF) to 512 (0x0200) which is the
    correct center for a 10-bit ADC. Fixes non-zero pitch/roll readings
    when no motion data is being passed through.
2025-12-23 Rename project from joypad-core to joypad-os
2025-12-23 Fix CI artifact organization for boards with underscores in names
2025-12-24 Bump version to 1.2.0

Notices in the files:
Membase/EAGLE/PCE128_Rev_C2_Main/PCE128_rev_C2.brd:
(C)2021 David Shadoff
PCFXMouse/EAGLE/FX_Ctrlr_Socket/rev_B/PCFX_Contrl_Socket_rev_B.brd:
(c) 2021, Dave Shadoff
res/hw/pcengine/EAGLE/rev_C/PCEMouse_rev_C.brd:
(C)2022 David Shadoff
parts and their libraries:
SparkFun-Connectors: Licensing: Creative Commons ShareAlike 4.0 International - https://creativecommons.org/licenses/by-sa/4.0
